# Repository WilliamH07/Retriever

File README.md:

<div align="center">

# Retriever

**Open source autonomous outdoor mobile robot**

[Architecture](docs/architecture/) ·
[Getting started](docs/DEMARRAGE.md) ·
[Bench reports](docs/bancs/) ·
[Hardware](hardware/) ·
[Support the project](#supporting-the-project)

</div>

---

## What this is

Retriever is a four wheel drive outdoor robot, built by one person and released
as open hardware. Its single objective is autonomous outdoor navigation with
ROS 2 Jazzy and Nav2, on a chassis anyone can reproduce from documented,
commodity parts.

It is an open rebuild inspired by the [Clearpath
Husky](https://clearpathrobotics.com/husky-a300-unmanned-ground-vehicle-robot/),
a reference platform in mobile robotics labs. The Husky is an excellent machine,
priced as a commercial product. Retriever asks a different question: how much of
that capability can one person reach from recovered and off the shelf parts, if
the engineering is done properly rather than cheaply?

The hardware is deliberately ordinary. The discipline applied to it is not: an
architecture dossier written before the first part was cut, a failure mode
analysis, a hardware safety chain no software can override, and a measurable
exit criterion at every stage.

## Status

<div align="center">

</div>

| Stage | Exit criterion | State |
|:-----:|----------------|-------|
| 1 | Architecture dossier and CAD complete | done |
| 2 | Chassis fabricated and assembled | done |
| 2b | First sensors published to ROS 2 over a transport agnostic link | done: [IMU](docs/bancs/imu.md) at 99.8 Hz, [lidar](docs/bancs/lidar.md) |
| 2c | Motor bench: hub motors driven from Foxglove | **current**: [coded, first spin due](docs/bancs/moteurs.md) |
| 3 | Three PCBs redesigned, power chain energised, no motor connected | next |
| 4 | Motors driven, wheels raised, all stop tests pass | planned |
| 5 | Autonomous outdoor navigation to a waypoint | planned |

Beyond stage 5, the plan is to mount a [Niryo
One](https://github.com/NiryoRobotics/niryo_one) arm and turn Retriever into a
mobile manipulator.

<div align="center">

</div>

## System architecture

<div align="center">

</div>

Three decisions shape everything else.

**A CAN bus, not USB, carries every command.** Four BLDC drivers chopping tens
of amps within 30 cm of the signal wiring make USB the wrong choice for the
control path: it is master slave, dynamically enumerated, with no frame
priority. CAN 2.0A at 500 kbit/s links the computer to every microcontroller.
USB is kept for high bandwidth perception, whose loss degrades the mission but
cannot cause dangerous motion. On the bench today the same frames travel over
serial; one Kconfig option and one launch parameter switch to CAN.

**The main computer never does real time.** It runs perception, localisation,
Nav2 and the mission, and produces setpoints. A dedicated safety
microcontroller decides whether they may be executed: the computer requests
arming, the safety node grants or refuses it.

**Safety is hardware, and independent of software.** Six stop levels, from a
100 ms software collision monitor down to a latching emergency stop and a
manual battery isolator. The last two contain no code at all.

<div align="center">

</div>

## Power

<div align="center">

</div>

The contactor is designed onto the power board rather than bought: a
`TPS4810-Q1` driving two opposed MOSFETs cuts a fault in 4.3 µs, draws 4 mW
instead of a coil's 2 to 8 W, and can test itself. The trade off is documented
in [`12-contacteur-statique.md`](docs/architecture/12-contacteur-statique.md).

## Hardware at a glance

| | |
|---|---|
| Configuration | 4WD skid steer, outdoor |
| Structure | Aluminium extrusion frame, laser cut panels, 3D printed mounts |
| Target mass | 35 kg in running order |
| Target speed | 1.5 m/s, slopes up to 10 % |
| Drivetrain | 4 × 6.5 inch hoverboard hub motors, 250 W each, 15 pole pairs |
| Motor drivers | 4 × ZS-X11H BLDC drivers, two per motor node |
| Battery | Xiaomi M365 Pro pack, 10S4P, 37 V nominal (30 to 42 V), 474 Wh |
| Endurance | about 2 h at 200 W average (estimate, 85 % depth of discharge) |
| Compute | Youyeetoo X1 (Celeron N5105), Ubuntu 24.04, ROS 2 Jazzy |
| Real time | 3 × ESP32 (SAFETY, MOTION front, MOTION rear) on CAN 2.0A, 500 kbit/s |
| Sensors | BNO085 IMU (SPI), YDLIDAR X4, GNSS; outdoor lidar and depth camera wanted |
| Localisation | GNSS, IMU and wheel odometry, dual EKF |
| Navigation | Nav2, collision monitor, twist mux |

## Repository layout

```
docs/
  architecture/   the design dossier: 00–07 base, 08–12 PCB and errata, 13 software
  bancs/          bench reports: IMU, lidar, motors (French)
  DEMARRAGE.md    getting started, from a blank machine to /imu/data (French)
  measurements/   bench measurements that gate the hardware design
  foxglove/       Foxglove Studio layouts for each bench
  images/         renders, build photos, diagrams
  sponsorship/    the sponsorship dossier
  archive/        superseded work, kept for history
hardware/
  icd.yaml        interface control document: every connector, every pin
  pcb/            the three boards, being redesigned
  cad/            laser cut DXF profiles, mechanical notes
  bom/            pointer to the costed bill of materials
firmware/
  protocol/       protocol.yaml, the single source of truth, and its generator
  components/     link layer, protocol header, BNO085 driver
  esp32_safety/   safety node (IMU bench today)
  esp32_motion/   motor node, front and rear
  test/           host tests, no hardware needed
ros2_ws/src/
  retriever_link/       transport agnostic bridge: serial today, SocketCAN later
  retriever_protocol/   generated protocol header for ROS 2
  retriever_msgs/       message definitions
  retriever_bringup/    launch files and bench configurations
  retriever_*           description, hardware, control, navigation, teleop: planned
tools/            bench scripts, flashing, protocol and link checks
```

## Documentation

The design documentation is in French; an English summary is planned. Every
claim carries a marker: verified against a datasheet, community consensus, to
be measured, or an explicit assumption.

| Start with | Why |
|---|---|
| [Documentation index](docs/README.md) | One page that says what each document is for and whether it is current |
| [Démarrage](docs/DEMARRAGE.md) | Install, flash an ESP32, build the workspace, verify the IMU chain stage by stage |
| [Bench reports](docs/bancs/) | What runs today, with measured numbers, and the silent defects found on the way |
| [Architecture dossier](docs/architecture/) | Power, communications, ROS 2, safety, network, BOM and FMEA, operator console |
| [Corrections v1.2](docs/architecture/11-corrections-v1.2.md) | Takes precedence over 00–07 wherever they disagree |

## Supporting the project

Retriever is self funded by a student. Four items stand between the current
platform and autonomous outdoor operation:

- **Printed circuit boards.** Three boards are being redesigned from a clean
  sheet: a motor interface, a safety and power board, and a passive CAN and
  safety bus distribution board.
- **Embedded AI compute.** The current x86 board runs the navigation stack, but
  not the perception outdoor autonomy asks for.
- **An outdoor lidar.** The blocking item. The 2D lidar on hand is specified for
  indoor use, and direct sunlight saturates its receiver.
- **A depth camera.** The Kinect v2 on hand is blind in daylight and its driver
  has been unmaintained since 2021.

Sponsors get a written and filmed integration tutorial for the sponsored part,
a field test video with honest performance data, attribution on the chassis and
here, and private feedback on how the part behaves on a real robot before
anything is published.

The full dossier is in [docs/sponsorship](docs/sponsorship/). Enquiries welcome:
see contact below.

## Credits

Inspired by the Clearpath Husky platform. The mechanical design was modelled
from scratch and the electrical and software architecture designed
independently. Some ROS 2 package conventions follow the open source
[husky/husky](https://github.com/husky/husky) repository, published under BSD 3
Clause. Clearpath Robotics is not affiliated with this project and does not
endorse it.

See [CREDITS.md](CREDITS.md) for the full attribution, and
[CONTRIBUTING.md](CONTRIBUTING.md) before opening a pull request.

## Licence

Software and firmware are released under the [Apache License 2.0](LICENSE).
Hardware designs, CAD and PCB files are released under the [CERN Open Hardware
Licence Version 2, Strongly Reciprocal](LICENSE-HARDWARE.txt).

## Contact

William Hanczyk, Bordeaux, France
wcontact33@gmail.com

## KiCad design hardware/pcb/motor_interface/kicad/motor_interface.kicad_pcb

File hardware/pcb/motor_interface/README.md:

# motor_interface

> **v2.0-draft — do not fabricate before M7, HALL_OC, P1, P2, P3.** Schematic and
> layout generated, ERC and DRC clean (ERC 0, DRC 0 with schematic parity and all severities, 0 unconnected). Every choice and its reason:
> [`decisions.md`](decisions.md) (French). Brief:
> [`cahier-des-charges.md`](cahier-des-charges.md).

| | |
|---|---|
| Size | 100 × 100 mm, 4 layers, 4 × M3, antenna notch on the right edge |
| Parts | 123 placed by the assembler (117 SMD + 6 Micro-Fit 6-way); hand-soldered: 2 × Micro-Fit 8-way, 2 × Mill-Max sockets; 14 option footprints not fitted; 20 named test pads |
| Module | ESP32-DevKitC V4 on two 1 × 19 turned-pin sockets, rows 25.40 mm apart (P1 to confirm) |
| Sources | [`kicad/`](kicad/) — KiCad 10 project, **generated** by [`scripts/build.py`](scripts/build.py) |
| Fabrication | [`fab/`](fab/) — Gerber zip, JLCPCB BOM and placement, schematic PDF, renders |

Rebuild everything: `./build.sh` (routing takes several minutes) then `./fab.sh`
(needs the toolchain in [`../outils.md`](../outils.md)). Do not edit the KiCad files
by hand: change `scripts/build.py` and rebuild.

Sits between a MOTION ESP32 and two ZS-X11H drivers with their hub motors. One
reference, two boards in service (front and rear), three spares from a lot of five.
The role is set by a solder jumper read through the ADS1115, not by GPIO straps.

The specification of record is
[`10-spec-motor-interface.md`](../../../docs/architecture/10-spec-motor-interface.md).
The earlier four-motor board is archived in
[`docs/archive/pcb-v1/`](../../../docs/archive/pcb-v1/).

## What changed against the specification (13 November 2026)

| Point | Spec / ICD v1.2 | This board | Why |
|---|---|---|---|
| `5V_BRAKE` | through J5/J6 pin 7, 2200 µF on board | **not on this board**, pin 7 NC | Decision D5: unplugging the board must keep the brake applied |
| Power input | J7 and trunk pin 1 | **trunk only**, J7 removed | One source, nothing to arbitrate |
| Grounds | undefined | **`GND`, `GND_MOT_A`, `GND_MOT_B` kept apart**, bench-only 0 Ω ties not fitted | Decision D4: single star point on `safety_power` |
| DAC supply | 5 V | **3.3 V**, internal 2.048 V reference, op-amp gain 2.5 | `MCP4728` VIH = 0.7 VDD, unreachable from a 3.3 V bus at 5 V |
| Low-side switches | `DMG1012T` (SOT-523) | **`AO3400A`** (SOT-23, JLCPCB basic) | 48 mΩ guaranteed at VGS 2.5 V, hand-reworkable |
| Polarity options | on `DIR`, `STOP`, `EL` | **`DIR` and `STOP` only** | Any option on `EL` could defeat the fail-safe |
| Hall PPTC | 30 mA on the pull-up tap | **removed** | Separate `+5V_MOT_A/B` nets; no PPTC of that size trips before the 78L05 |
| Hall activity LEDs | six | **none** | Test points and the serial console do the same job |

## Scope

| Function | Implementation |
|---|---|
| Hall passthrough | J1→J3, J2→J4: five straight 0.8 mm tracks each, one layer, no via, no part in series |
| Hall tap | 2.2 kΩ pull-up (population option, HALL_OC), 2.2 kΩ + 10 nF / 100 V, `BAT54S` clamp, referenced to `GND_MOT_x`; `SN74LVC3G17` at 3.3 V (Ioff) |
| Speed command | `MCP4728` (3.3 V, internal ref.) → `TLV9062` ×2.5 → `VR`, 0 V with the module out |
| `DIR`, `STOP` | `AO3400A` open drain, gate pull-down; pull-up / pull-down / direct-drive footprints not fitted |
| Brake `EL` | per wheel `74LVC1G08` (`GPIO26` AND `/SAFE`) → `AO3400A`; pull-up on the harness |
| Temperatures, role, revision | `ADS1115` at 0x48: NTC A, NTC B, role divider (SJ1/SJ2), revision divider (½ = v2.0) |
| Watchdog | `TPL5010`, 2 s, `RSTn` on the module `EN` (D7) |
| CAN | `TCAN1042HVDR`, `STB` grounded, `VIO` 3.3 V, `NUP2105L`, `ACT45B`, no termination |
| Power | trunk 5 V → `AO3401A` reverse protection → `SMAJ6.0A` → `LM66100` → module 5 V; 3.3 V from the module |

## Blocking measurements

M7 (Hall output level and impedance), HALL_OC (open collector or push-pull),
HALL_COL (wire colours, silkscreen), P1 to P3 on the ESP32 module (row spacing, pin
order, PSRAM variant). See [`docs/measurements/`](../../../docs/measurements/).

Pinout: `boards.motor_interface` in [`hardware/icd.yaml`](../../icd.yaml) (v1.2; the
changes this board needs for v1.3 are listed at the end of [`decisions.md`](decisions.md)).

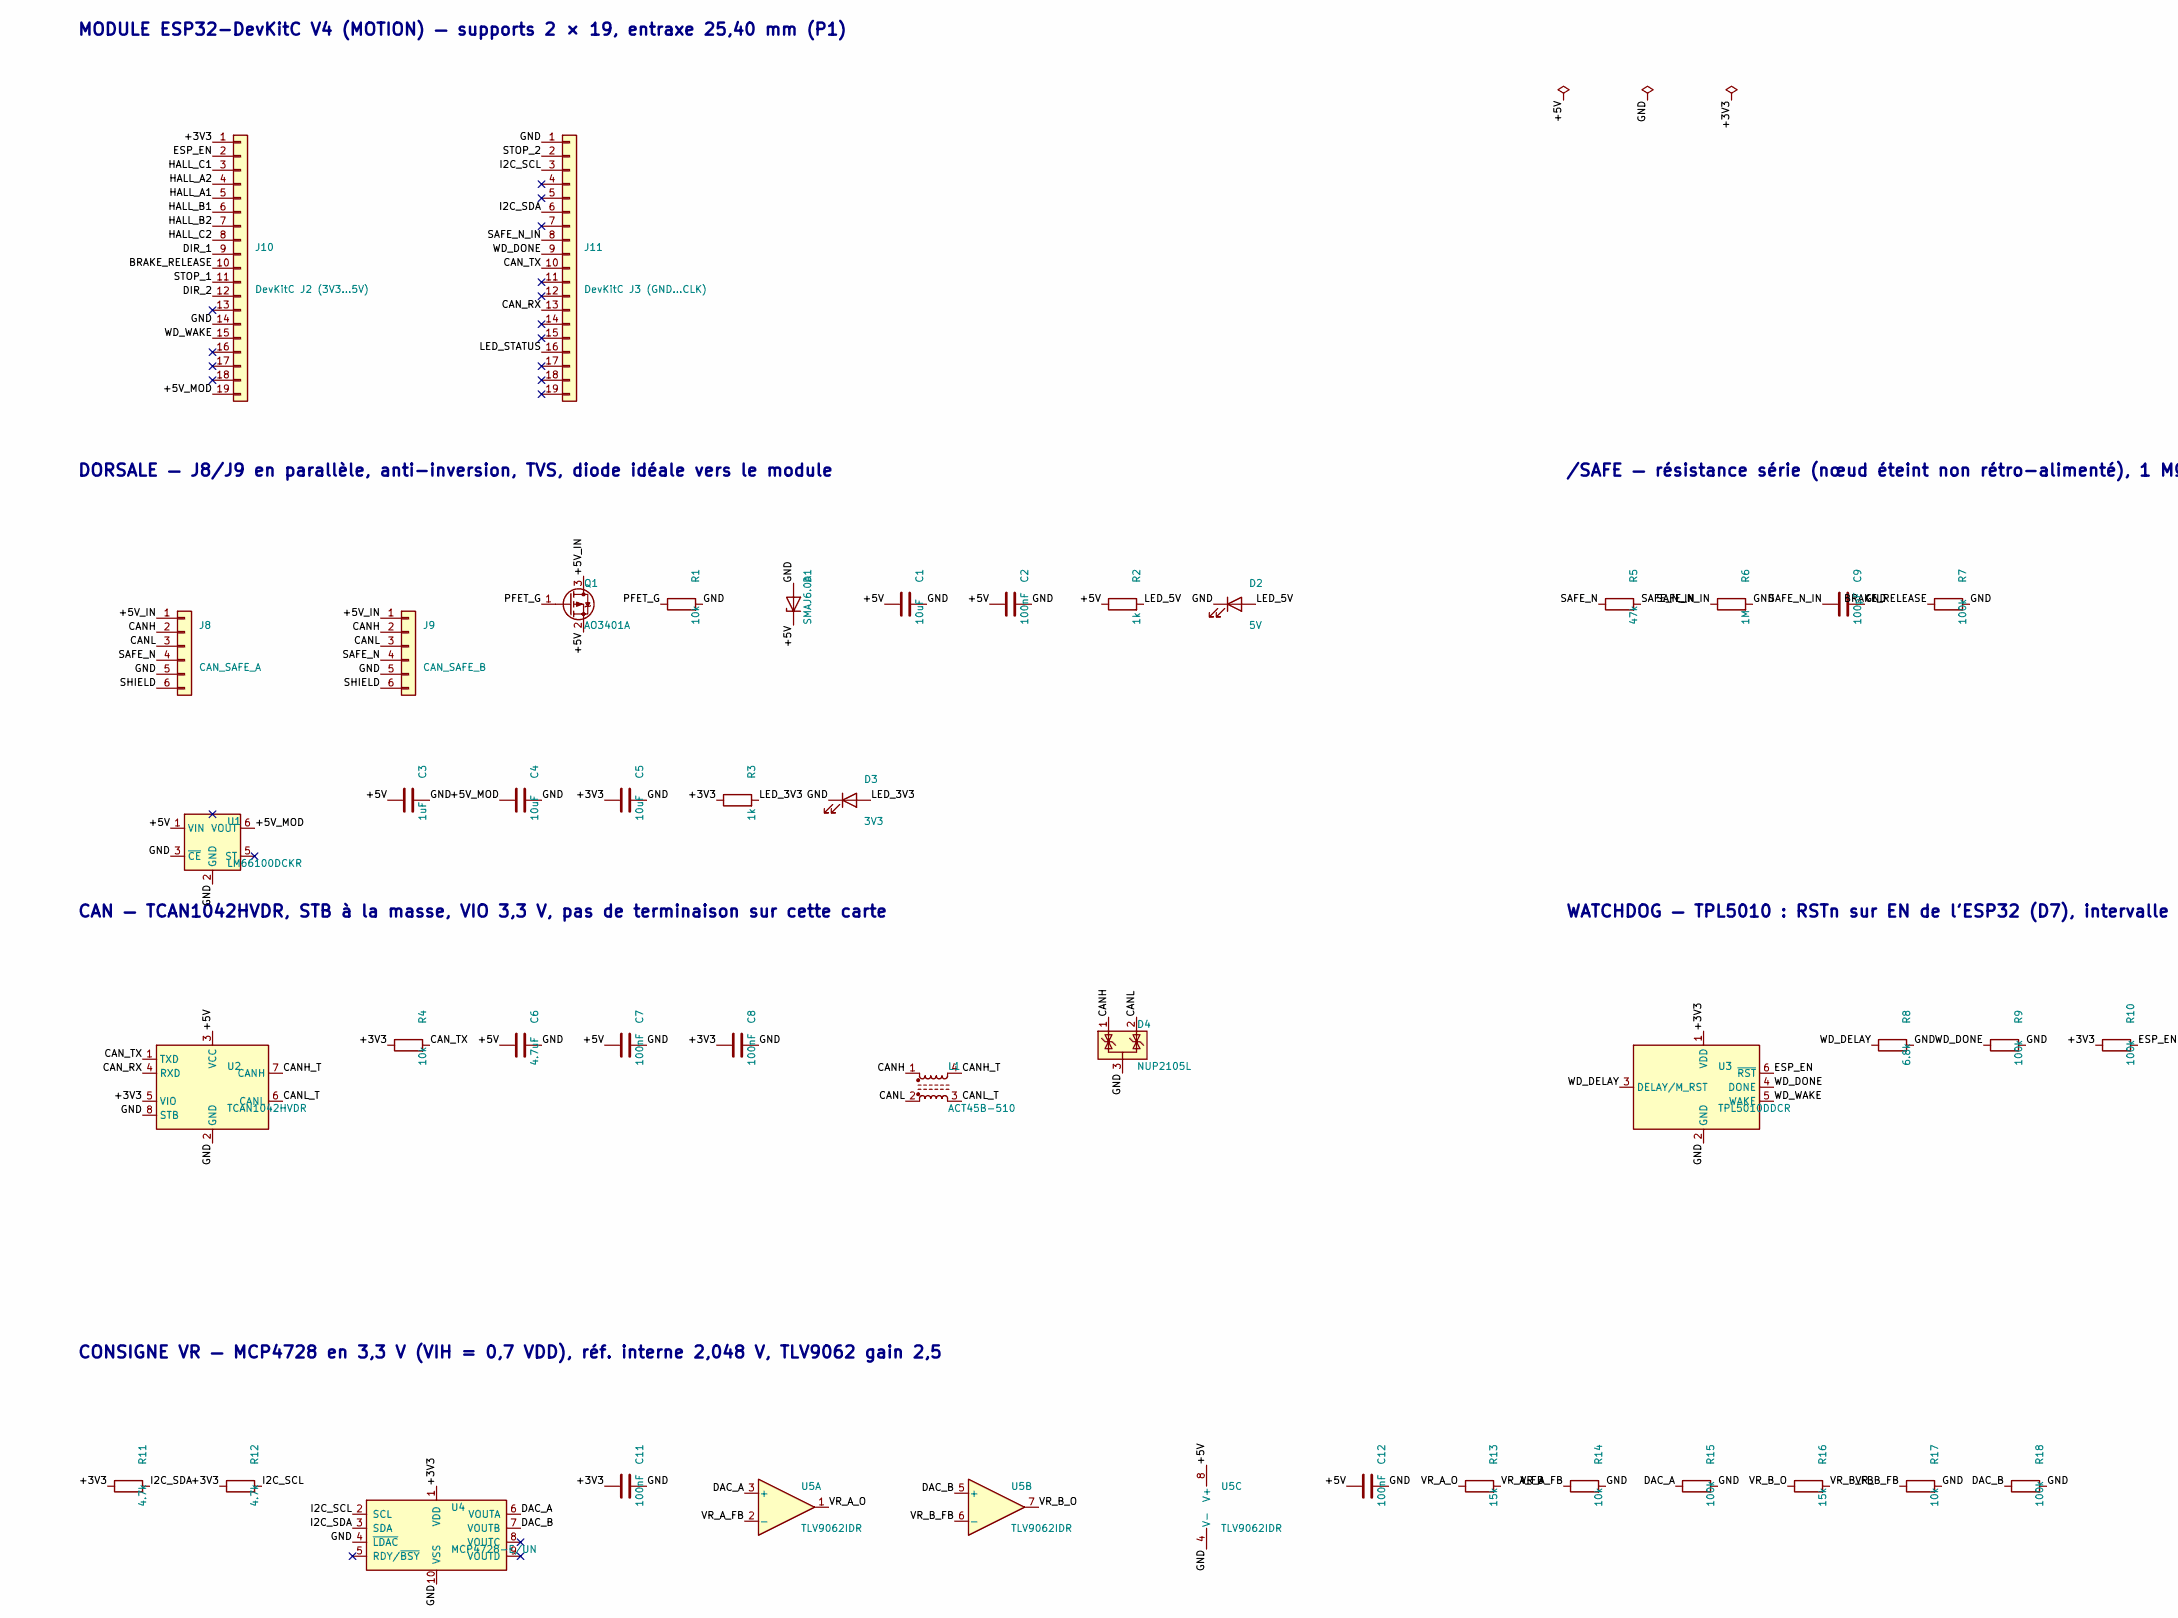
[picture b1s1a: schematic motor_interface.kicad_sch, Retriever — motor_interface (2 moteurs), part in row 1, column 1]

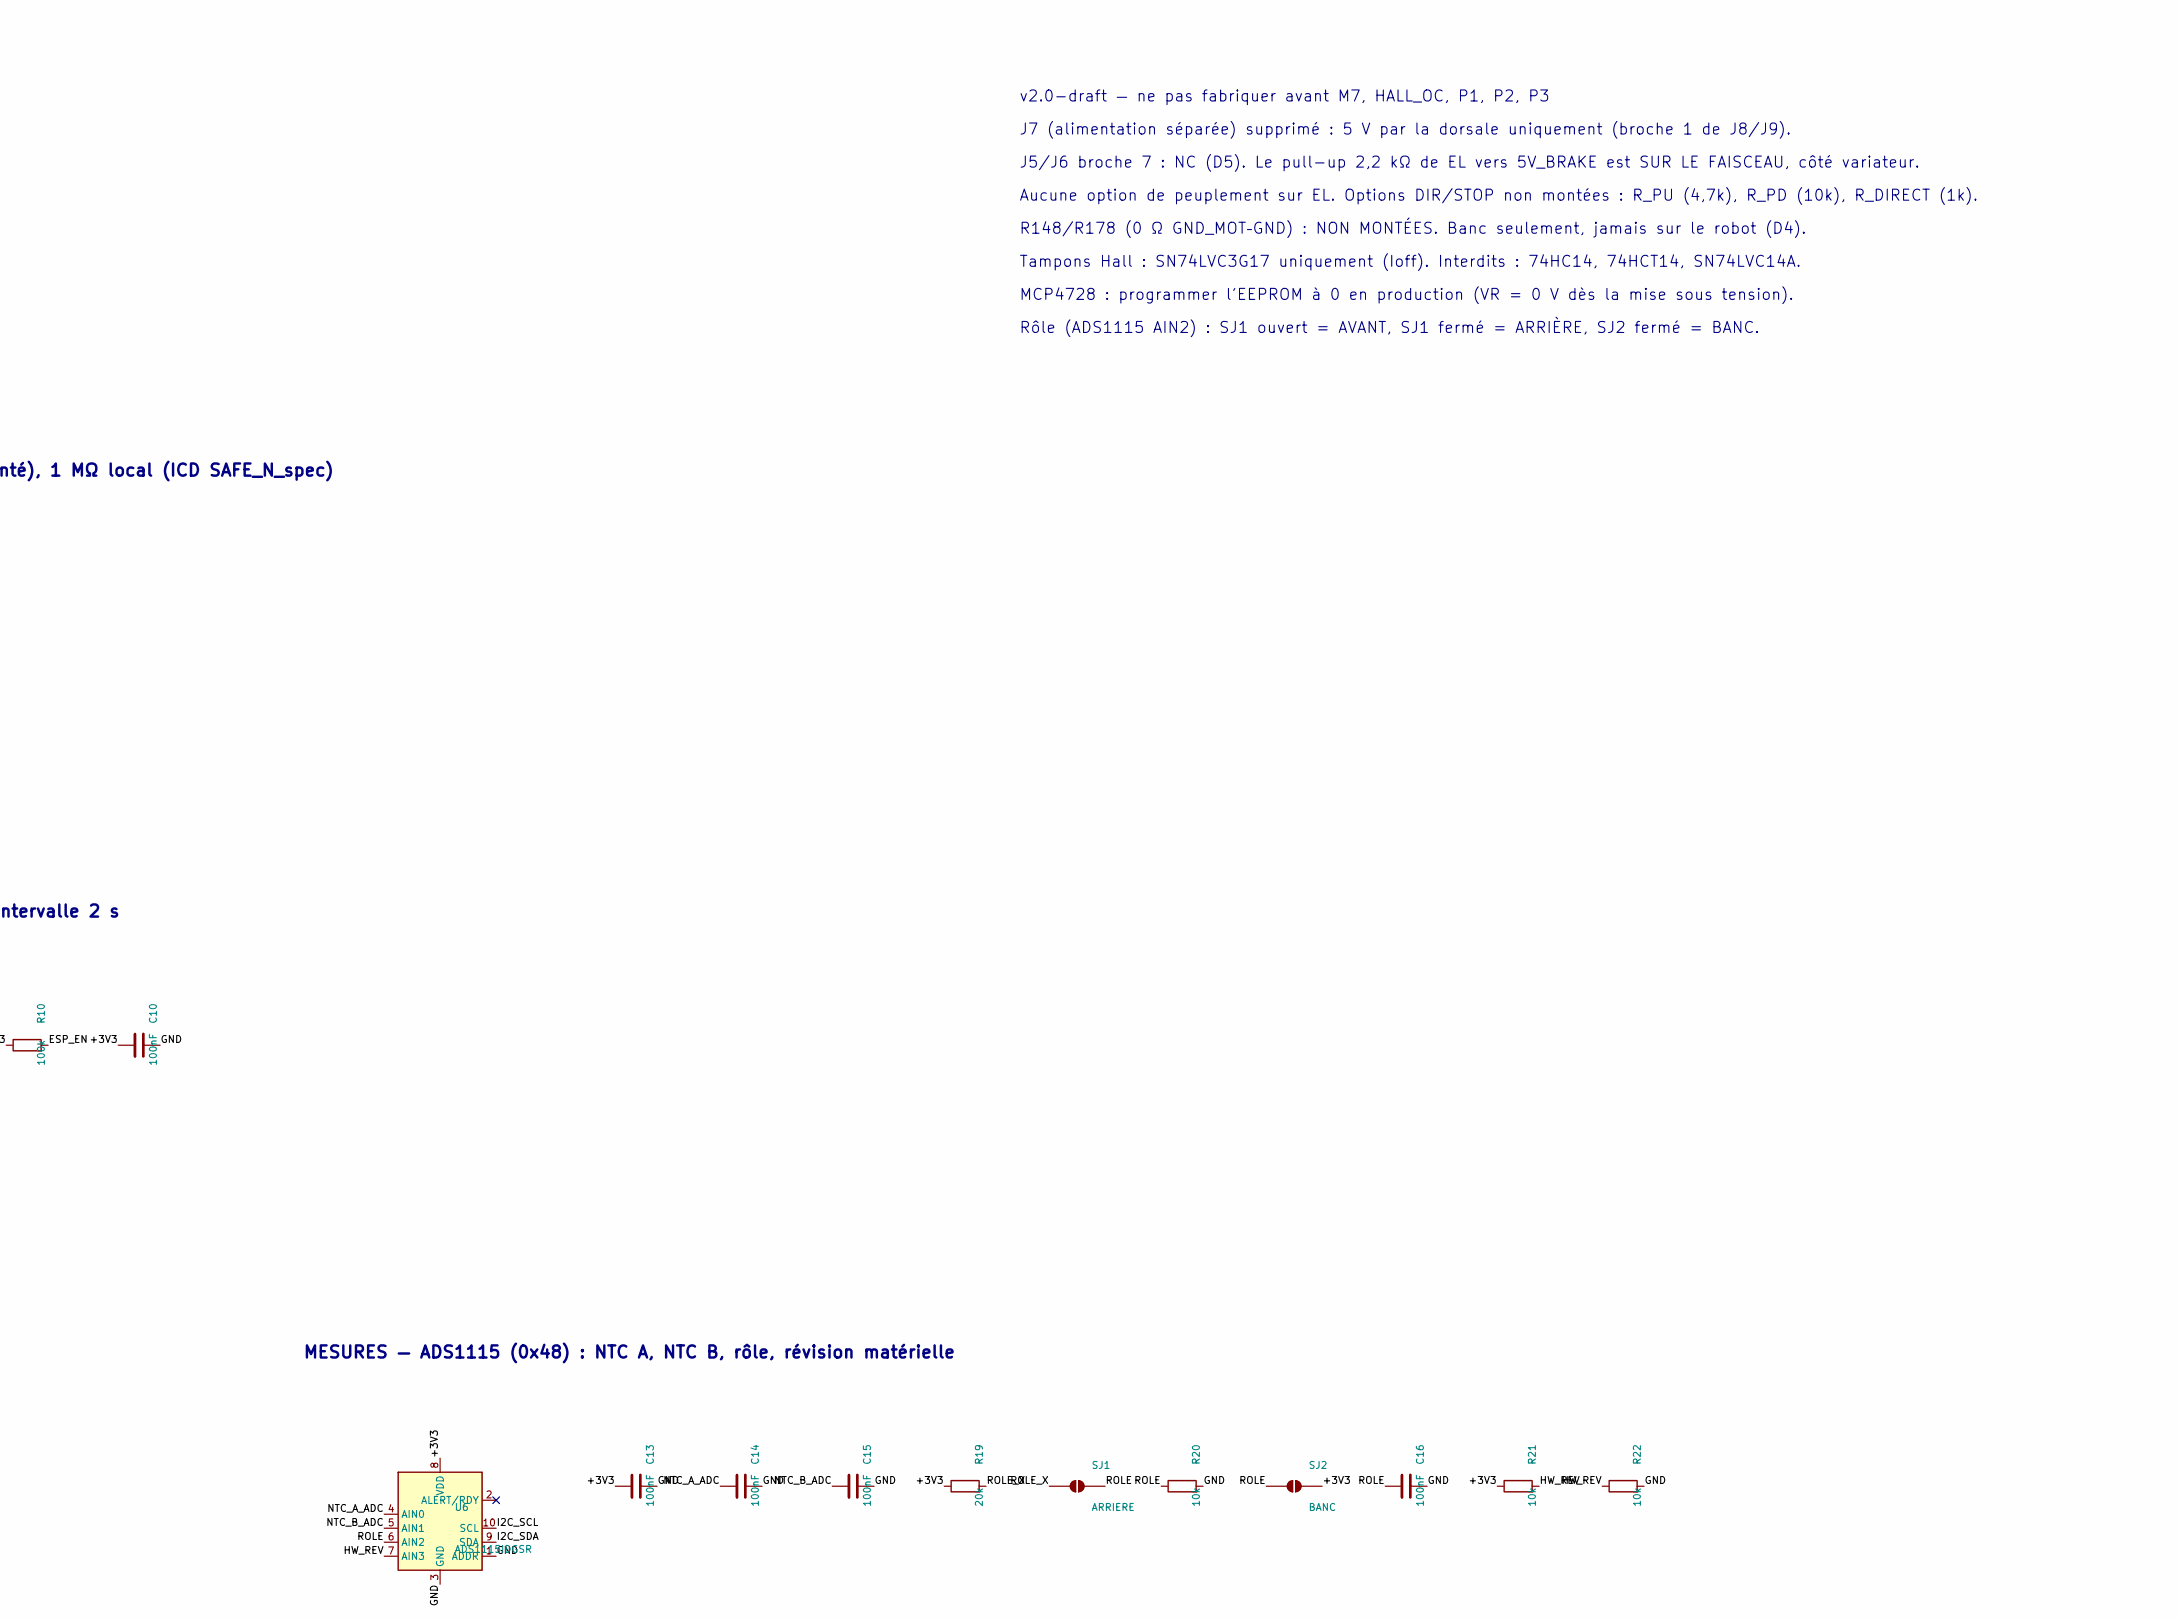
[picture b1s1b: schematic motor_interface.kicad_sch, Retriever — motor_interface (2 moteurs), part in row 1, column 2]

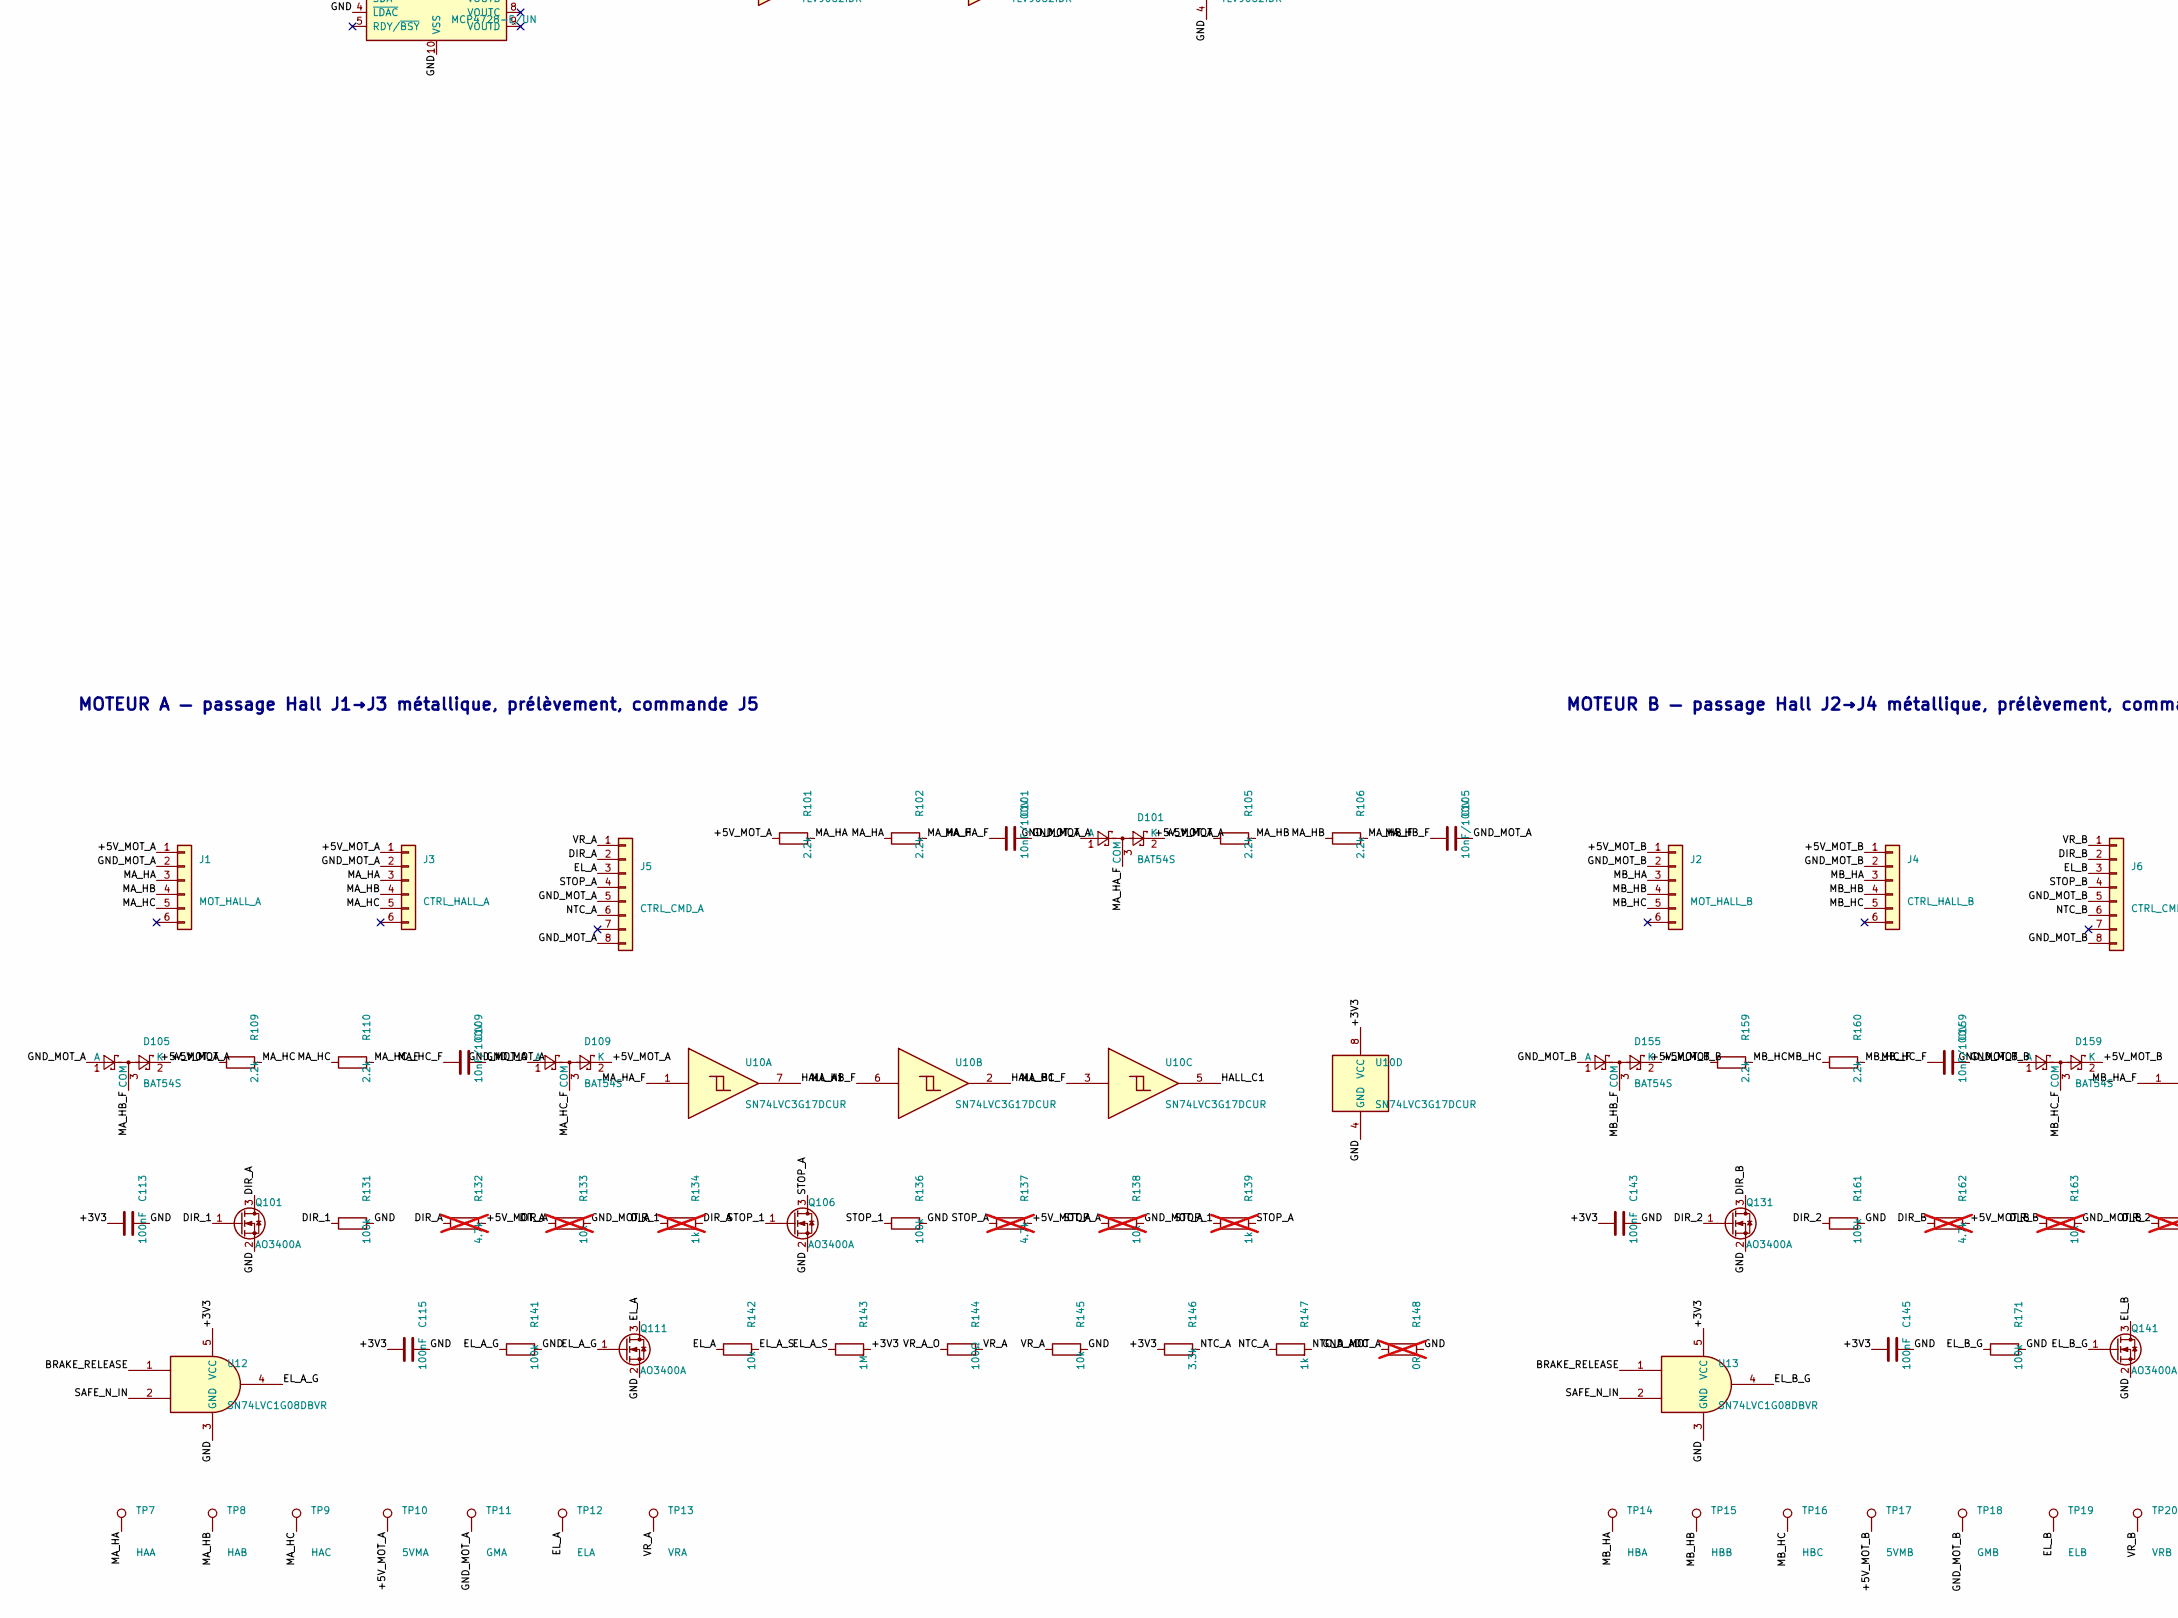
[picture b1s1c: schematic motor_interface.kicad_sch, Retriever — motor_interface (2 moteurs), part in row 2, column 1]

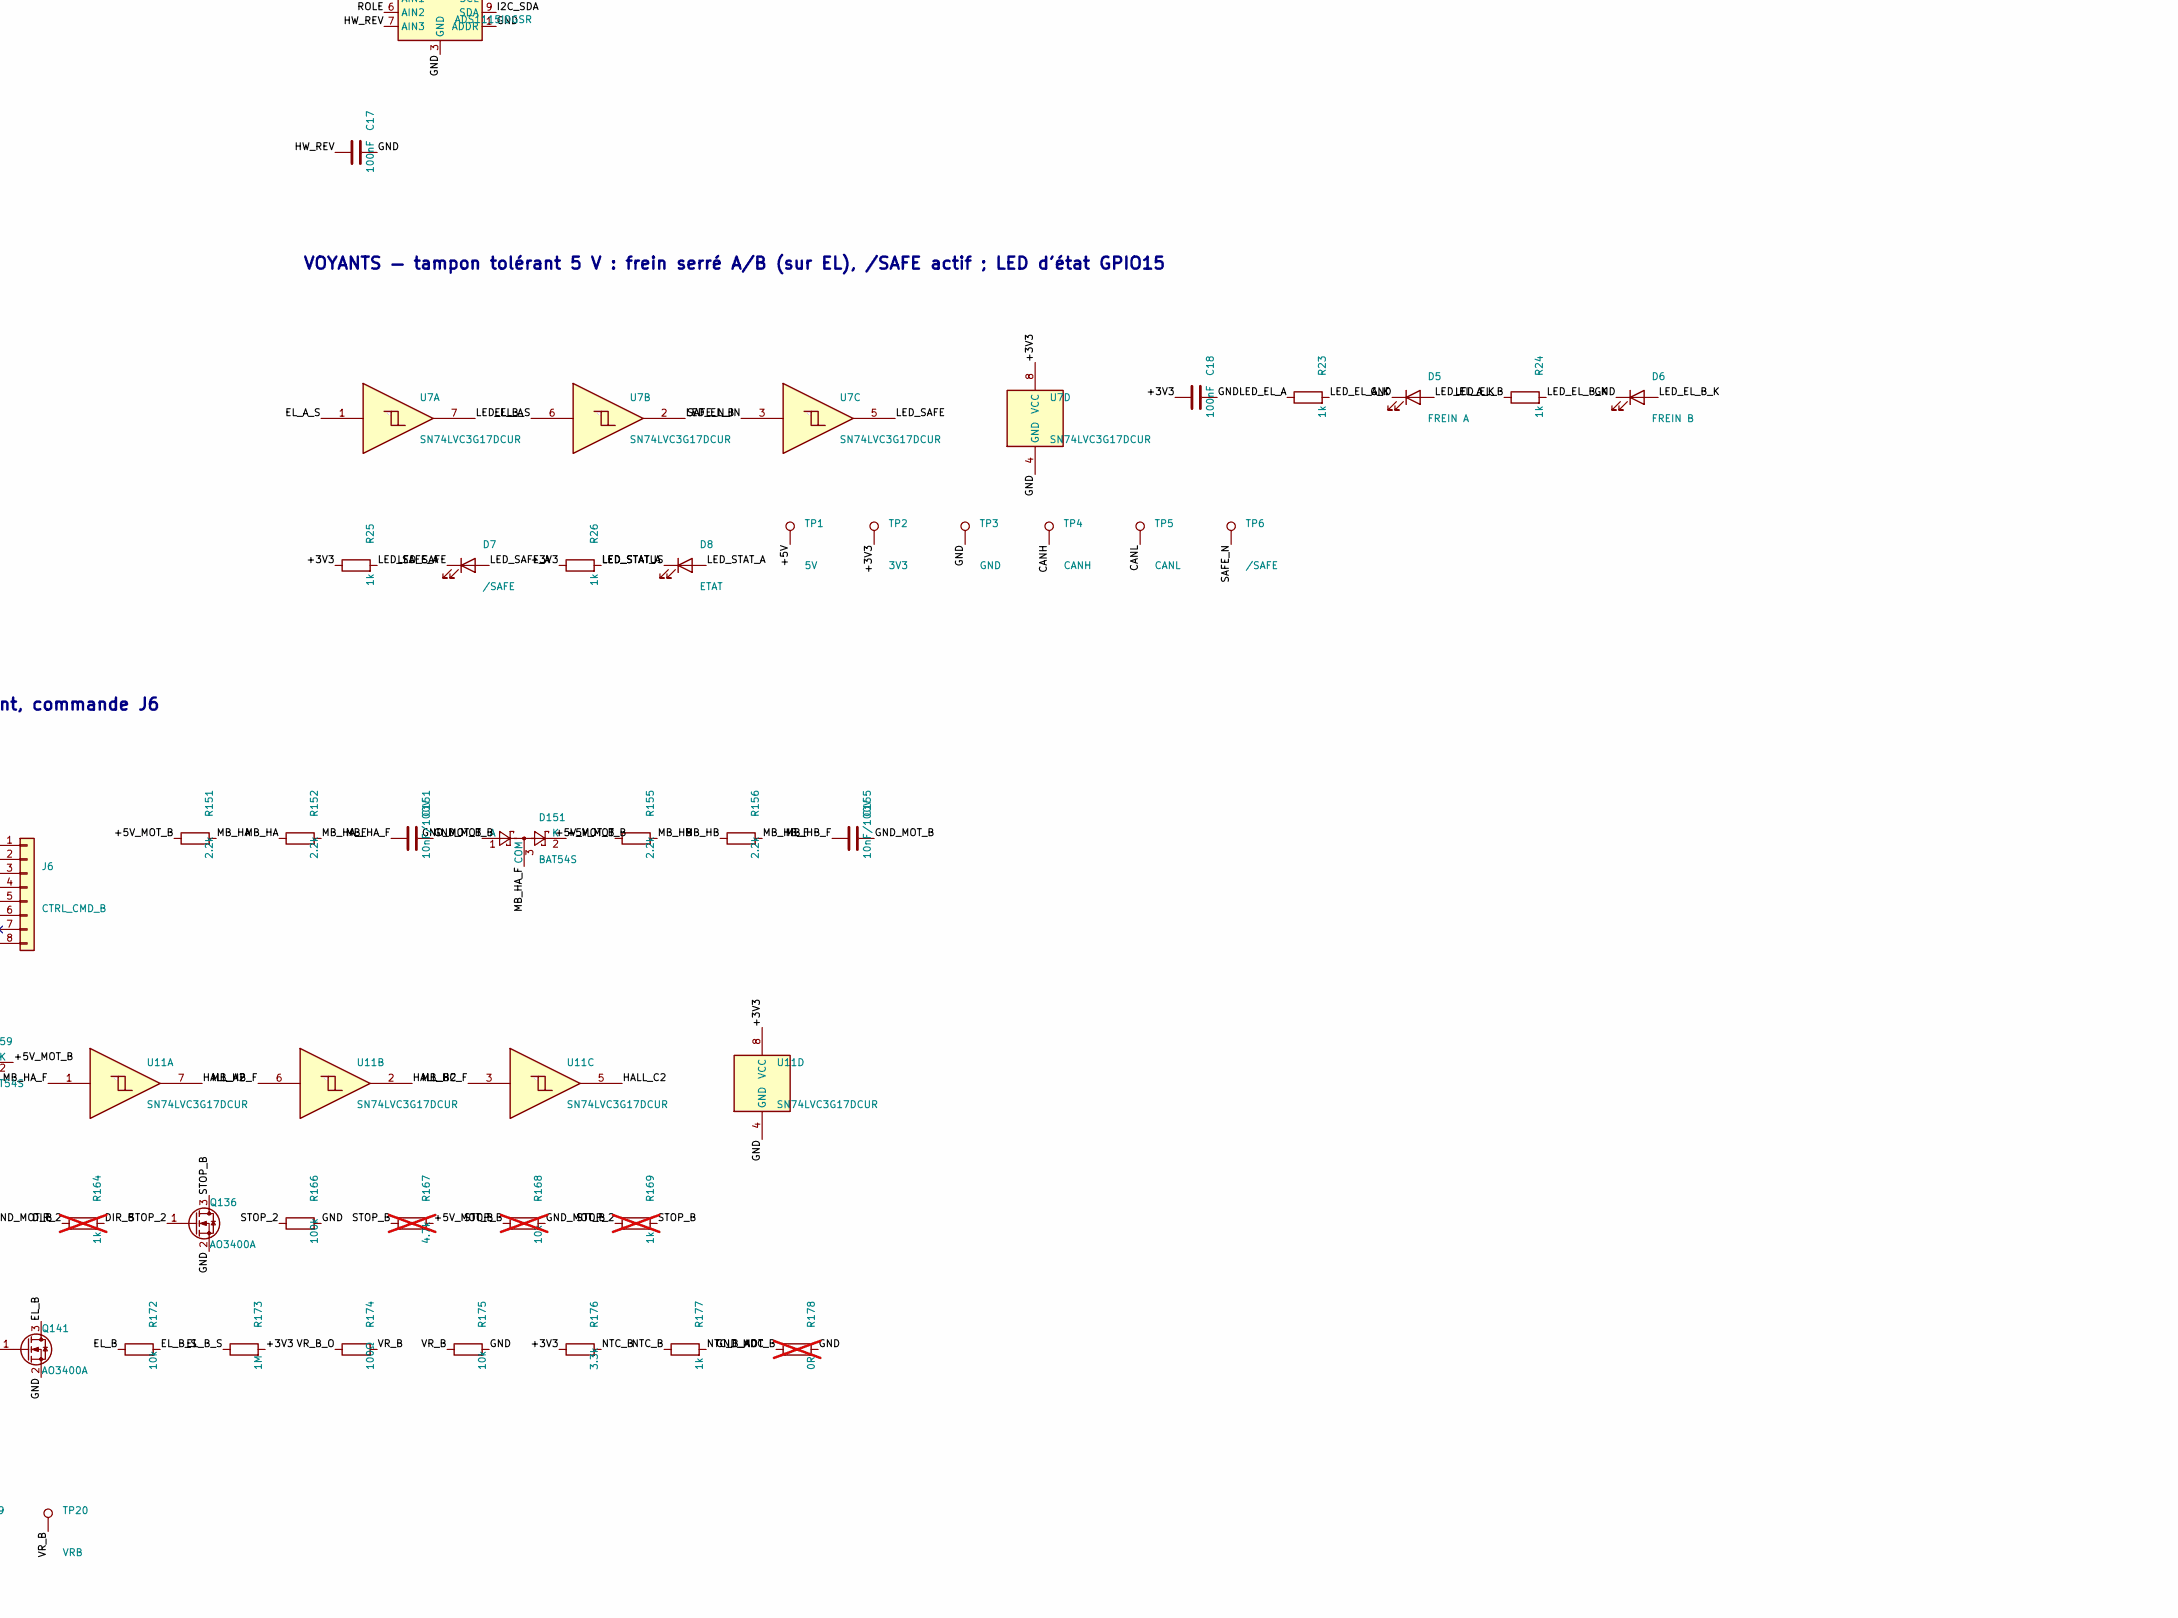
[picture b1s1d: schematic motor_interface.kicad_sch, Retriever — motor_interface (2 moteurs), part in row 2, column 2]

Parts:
C1, C4, C5: 10uF; C_0805_2012Metric; MPN CL21A106KAYNNNE; LCSC C15850
C2, C7, C8, C10, C11, C12, C13, C14, C15, C16, C17, C18, C113, C115, C143, C145: 100nF; C_0603_1608Metric; MPN CC0603KRX7R9BB104; LCSC C14663
C3: 1uF; C_0603_1608Metric; MPN CL10A105KB8NNNC; LCSC C15849
C6: 4.7uF; C_0805_2012Metric; MPN CL21A475KAQNNNE; LCSC C1779
C9: 100pF; C_0603_1608Metric; MPN CC0603JRNPO9BN101; LCSC C14858
C101, C105, C109, C151, C155, C159: 10nF/100V; C_0603_1608Metric; MPN FH 0603B103K101NT; LCSC C43253
D1: SMAJ6.0A; D_SMA; MPN Littelfuse SMAJ6.0A; LCSC C223993
D2: 5V; LED_0603_1608Metric; MPN Everlight 19-217/GHC; LCSC C72043
D3: 3V3; LED_0603_1608Metric; MPN Everlight 19-217/GHC; LCSC C72043
D4: NUP2105L; SOT-23; MPN onsemi NUP2105LT1G; LCSC C14486
D5: FREIN A; LED_0603_1608Metric; MPN Hubei KENTO KT-0603R; LCSC C2286
D6: FREIN B; LED_0603_1608Metric; MPN Hubei KENTO KT-0603R; LCSC C2286
D7: /SAFE; LED_0603_1608Metric; MPN Hubei KENTO KT-0603R; LCSC C2286
D8: ETAT; LED_0603_1608Metric; MPN Everlight 19-217/BHC; LCSC C72041
D101, D105, D109, D151, D155, D159: BAT54S; SOT-23; MPN Nexperia BAT54S,215; LCSC C47546
J1: MOT_HALL_A; Molex_Micro-Fit_3.0_43650-0615_1x06_P3.00mm_Vertical; MPN Molex 43650-0615; LCSC C505231
J2: MOT_HALL_B; Molex_Micro-Fit_3.0_43650-0615_1x06_P3.00mm_Vertical; MPN Molex 43650-0615; LCSC C505231
J3: CTRL_HALL_A; Molex_Micro-Fit_3.0_43650-0615_1x06_P3.00mm_Vertical; MPN Molex 43650-0615; LCSC C505231
J4: CTRL_HALL_B; Molex_Micro-Fit_3.0_43650-0615_1x06_P3.00mm_Vertical; MPN Molex 43650-0615; LCSC C505231
J5: CTRL_CMD_A; Molex_Micro-Fit_3.0_43650-0815_1x08_P3.00mm_Vertical; MPN Molex 43650-0815 (Mouser 538-43650-0815)
J6: CTRL_CMD_B; Molex_Micro-Fit_3.0_43650-0815_1x08_P3.00mm_Vertical; MPN Molex 43650-0815 (Mouser 538-43650-0815)
J8: CAN_SAFE_A; Molex_Micro-Fit_3.0_43650-0615_1x06_P3.00mm_Vertical; MPN Molex 43650-0615; LCSC C505231
J9: CAN_SAFE_B; Molex_Micro-Fit_3.0_43650-0615_1x06_P3.00mm_Vertical; MPN Molex 43650-0615; LCSC C505231
J10: DevKitC J2 (3V3…5V); PinSocket_1x19_P2.54mm_Vertical; MPN Mill-Max 310-43-119-41-001000 (Mouser)
J11: DevKitC J3 (GND…CLK); PinSocket_1x19_P2.54mm_Vertical; MPN Mill-Max 310-43-119-41-001000 (Mouser)
L1: ACT45B-510; IND-SMD_4P-L4.5-W3.2-TL; MPN TDK ACT45B-510-2P-TL003; LCSC C76584
Q1: AO3401A; SOT-23; MPN AOS AO3401A; LCSC C15127
Q101, Q106, Q111, Q131, Q136, Q141: AO3400A; SOT-23; MPN AOS AO3400A; LCSC C20917
R1, R4, R14, R17, R20, R21, R22, R142, R145, R172, R175: 10k; R_0603_1608Metric; MPN 0603WAF1002T5E; LCSC C25804
R2, R3, R23, R24, R25, R26, R147, R177: 1k; R_0603_1608Metric; MPN 0603WAF1001T5E; LCSC C21190
R5: 47k; R_0603_1608Metric; MPN 0603WAF4702T5E; LCSC C25819
R6, R143, R173: 1M; R_0603_1608Metric; MPN 0603WAF1004T5E; LCSC C22935
R7, R9, R10, R15, R18, R131, R136, R141, R161, R166, R171: 100k; R_0603_1608Metric; MPN 0603WAF1003T5E; LCSC C25803
R8: 6.8k; R_0603_1608Metric; MPN 0603WAF6801T5E; LCSC C23212
R11, R12: 4.7k; R_0603_1608Metric; MPN 0603WAF4701T5E; LCSC C23162
R13, R16: 15k; R_0603_1608Metric; MPN 0603WAF1502T5E; LCSC C22809
R19: 20k; R_0603_1608Metric; MPN 0603WAF2002T5E; LCSC C4184
R101, R102, R105, R106, R109, R110, R151, R152, R155, R156, R159, R160: 2.2k; R_0603_1608Metric; MPN 0603WAF2201T5E; LCSC C4190
R132, R137, R162, R167: 4.7k; R_0603_1608Metric; MPN 0603WAF4701T5E; LCSC C23162; not fitted
R133, R138, R163, R168: 10k; R_0603_1608Metric; MPN 0603WAF1002T5E; LCSC C25804; not fitted
R134, R139, R164, R169: 1k; R_0603_1608Metric; MPN 0603WAF1001T5E; LCSC C21190; not fitted
R144, R174: 100Ω; R_0603_1608Metric; MPN 0603WAF1000T5E; LCSC C22775
R146, R176: 3.3k; R_0603_1608Metric; MPN 0603WAF3301T5E; LCSC C22978
R148, R178: 0R; R_0603_1608Metric; MPN 0603WAF0000T5E; LCSC C21189; not fitted
SJ1: ARRIERE; SolderJumper-2_P1.3mm_Open_RoundedPad1.0x1.5mm
SJ2: BANC; SolderJumper-2_P1.3mm_Open_RoundedPad1.0x1.5mm
TP1: 5V; TestPoint_Pad_D1.5mm
TP2: 3V3; TestPoint_Pad_D1.5mm
TP3: GND; TestPoint_Pad_D1.5mm
TP4: CANH; TestPoint_Pad_D1.5mm
TP5: CANL; TestPoint_Pad_D1.5mm
TP6: /SAFE; TestPoint_Pad_D1.5mm
TP7: HAA; TestPoint_Pad_D1.5mm
TP8: HAB; TestPoint_Pad_D1.5mm
TP9: HAC; TestPoint_Pad_D1.5mm
TP10: 5VMA; TestPoint_Pad_D1.5mm
TP11: GMA; TestPoint_Pad_D1.5mm
TP12: ELA; TestPoint_Pad_D1.5mm
TP13: VRA; TestPoint_Pad_D1.5mm
TP14: HBA; TestPoint_Pad_D1.5mm
TP15: HBB; TestPoint_Pad_D1.5mm
TP16: HBC; TestPoint_Pad_D1.5mm
TP17: 5VMB; TestPoint_Pad_D1.5mm
TP18: GMB; TestPoint_Pad_D1.5mm
TP19: ELB; TestPoint_Pad_D1.5mm
TP20: VRB; TestPoint_Pad_D1.5mm
U1: LM66100DCKR; SOT-363_SC-70-6; MPN TI LM66100DCKR; LCSC C2869734
U2: TCAN1042HVDR; SOIC-8_3.9x4.9mm_P1.27mm; MPN TI TCAN1042HVDR; LCSC C127869
U3: TPL5010DDCR; SOT-23-6; MPN TI TPL5010DDCR; LCSC C473912
U4: MCP4728-E/UN; MSOP-10_3x3mm_P0.5mm; MPN Microchip MCP4728-E/UN; LCSC C108207
U5: TLV9062IDR; SOIC-8_3.9x4.9mm_P1.27mm; MPN TI TLV9062IDR; LCSC C398355
U6: ADS1115IDGSR; TSSOP-10_3x3mm_P0.5mm; MPN TI ADS1115IDGSR; LCSC C37593
U7, U10, U11: SN74LVC3G17DCUR; VSSOP-8_2.3x2mm_P0.5mm; MPN TI SN74LVC3G17DCUR; LCSC C68245
U12, U13: SN74LVC1G08DBVR; SOT-23-5; MPN TI SN74LVC1G08DBVR; LCSC C7666

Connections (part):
/+3V3: C5.1, C8.1, C10.1, C11.1, C13.1, C18.1, C113.1, C115.1, C143.1, C145.1, J10.1, R3.1, R4.1, R10.1, R11.1, R12.1, R19.1, R21.1, R25.1, R26.1, R143.2, R146.1, R173.2, R176.1, SJ2.2 (B), TP2.1, U2.5 (VIO), U3.1 (VDD), U4.1 (VDD), U6.8 (VDD), U7.8 (VCC), U10.8 (VCC), U11.8 (VCC), U12.5 (VCC), U13.5 (VCC)
/+5V: C1.1, C2.1, C3.1, C6.1, C7.1, C12.1, D1.1 (K), Q1.2 (S), R2.1, TP1.1, U1.1 (VIN), U2.3 (VCC), U5.8 (V+)
/+5V_IN: J8.1, J9.1, Q1.3 (D)
/+5V_MOD: C4.1, J10.19, U1.6 (VOUT)
/+5V_MOT_A: D101.2 (K), D105.2 (K), D109.2 (K), J1.1, J3.1, R101.1, R105.1, R109.1, R132.2, R137.2, TP10.1
/+5V_MOT_B: D151.2 (K), D155.2 (K), D159.2 (K), J2.1, J4.1, R151.1, R155.1, R159.1, R162.2, R167.2, TP17.1
/BRAKE_RELEASE: J10.10, R7.1, U12.1, U13.1
/CANH: D4.1 (K), J8.2, J9.2, L1.1, TP4.1
/CANH_T: L1.4, U2.7 (CANH)
/CANL: D4.2 (K), J8.3, J9.3, L1.2, TP5.1
/CANL_T: L1.3, U2.6 (CANL)
/CAN_RX: J11.13, U2.4 (RXD)
/CAN_TX: J11.10, R4.2, U2.1 (TXD)
/DAC_A: R15.1, U4.6 (VOUTA), U5.3 (+)
/DAC_B: R18.1, U4.7 (VOUTB), U5.5 (+)
/DIR_1: J10.9, Q101.1 (G), R131.1, R134.1
/DIR_2: J10.12, Q131.1 (G), R161.1, R164.1
/DIR_A: J5.2, Q101.3 (D), R132.1, R133.1, R134.2
/DIR_B: J6.2, Q131.3 (D), R162.1, R163.1, R164.2
/EL_A: J5.3, Q111.3 (D), R142.1, TP12.1
/EL_A_G: Q111.1 (G), R141.1, U12.4
/EL_A_S: R142.2, R143.1, U7.1
/EL_B: J6.3, Q141.3 (D), R172.1, TP19.1
/EL_B_G: Q141.1 (G), R171.1, U13.4
/EL_B_S: R172.2, R173.1, U7.6
/ESP_EN: J10.2, R10.2, U3.6 (~RST)
/GND: C1.2, C2.2, C3.2, C4.2, C5.2, C6.2, C7.2, C8.2, C9.2, C10.2, C11.2, C12.2, C13.2, C14.2, C15.2, C16.2, C17.2, C18.2, C113.2, C115.2, C143.2, C145.2, D1.2 (A), D2.1 (K), D3.1 (K), D4.3 (A), D5.1 (K), D6.1 (K), J8.5, J9.5, J10.14, J11.1, Q101.2 (S), Q106.2 (S), Q111.2 (S), Q131.2 (S), Q136.2 (S), Q141.2 (S), R1.2, R6.2, R7.2, R8.2, R9.2, R14.2, R15.2, R17.2, R18.2, R20.2, R22.2, R131.2, R136.2, R141.2, R145.2, R148.2, R161.2, R166.2, R171.2, R175.2, R178.2, TP3.1, U1.2 (GND), U1.3 (~CE), U2.2 (GND), U2.8 (STB), U3.2 (GND), U4.4 (~LDAC), U4.10 (VSS), U5.4 (V-), U6.1 (ADDR), U6.3 (GND), U7.4 (GND), U10.4 (GND), U11.4 (GND), U12.3 (GND), U13.3 (GND)
/GND_MOT_A: C101.2, C105.2, C109.2, D101.1 (A), D105.1 (A), D109.1 (A), J1.2, J3.2, J5.5, J5.8, R133.2, R138.2, R148.1, TP11.1
/GND_MOT_B: C151.2, C155.2, C159.2, D151.1 (A), D155.1 (A), D159.1 (A), J2.2, J4.2, J6.5, J6.8, R163.2, R168.2, R178.1, TP18.1
/HALL_A1: J10.5, U10.7
/HALL_A2: J10.4, U11.7
/HALL_B1: J10.6, U10.2
/HALL_B2: J10.7, U11.2
/HALL_C1: J10.3, U10.5
/HALL_C2: J10.8, U11.5
/HW_REV: C17.1, R21.2, R22.1, U6.7 (AIN3)
/I2C_SCL: J11.3, R12.2, U4.2 (SCL), U6.10 (SCL)
/I2C_SDA: J11.6, R11.2, U4.3 (SDA), U6.9 (SDA)
/LED_3V3: D3.2 (A), R3.2
/LED_5V: D2.2 (A), R2.2
/LED_EL_A: R23.1, U7.7
/LED_EL_A_K: D5.2 (A), R23.2
/LED_EL_B: R24.1, U7.2
/LED_EL_B_K: D6.2 (A), R24.2
/LED_SAFE: D7.1 (K), U7.5
/LED_SAFE_A: D7.2 (A), R25.2
/LED_STATUS: D8.1 (K), J11.16
/LED_STAT_A: D8.2 (A), R26.2
/MA_HA: J1.3, J3.3, R101.2, R102.1, TP7.1
/MA_HA_F: C101.1, D101.3 (COM), R102.2, U10.1
/MA_HB: J1.4, J3.4, R105.2, R106.1, TP8.1
/MA_HB_F: C105.1, D105.3 (COM), R106.2, U10.6
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
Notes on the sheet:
MODULE ESP32-DevKitC V4 (MOTION) — supports 2 × 19, entraxe 25,40 mm (P1)
DORSALE — J8/J9 en parallèle, anti-inversion, TVS, diode idéale vers le module
CAN — TCAN1042HVDR, STB à la masse, VIO 3,3 V, pas de terminaison sur cette carte
/SAFE — résistance série (nœud éteint non rétro-alimenté), 1 MΩ local (ICD SAFE_N_spec)
WATCHDOG — TPL5010 : RSTn sur EN de l'ESP32 (D7), intervalle 2 s
CONSIGNE VR — MCP4728 en 3,3 V (VIH = 0,7 VDD), réf. interne 2,048 V, TLV9062 gain 2,5
MESURES — ADS1115 (0x48) : NTC A, NTC B, rôle, révision matérielle
VOYANTS — tampon tolérant 5 V : frein serré A/B (sur EL), /SAFE actif ; LED d'état GPIO15
MOTEUR A — passage Hall J1→J3 métallique, prélèvement, commande J5
MOTEUR B — passage Hall J2→J4 métallique, prélèvement, commande J6
v2.0-draft — ne pas fabriquer avant M7, HALL_OC, P1, P2, P3
J7 (alimentation séparée) supprimé : 5 V par la dorsale uniquement (broche 1 de J8/J9).
J5/J6 broche 7 : NC (D5). Le pull-up 2,2 kΩ de EL vers 5V_BRAKE est SUR LE FAISCEAU, côté variateur.
Aucune option de peuplement sur EL. Options DIR/STOP non montées : R_PU (4,7k), R_PD (10k), R_DIRECT (1k).
R148/R178 (0 Ω GND_MOT–GND) : NON MONTÉES. Banc seulement, jamais sur le robot (D4).
Tampons Hall : SN74LVC3G17 uniquement (Ioff). Interdits : 74HC14, 74HCT14, SN74LVC14A.
MCP4728 : programmer l'EEPROM à 0 en production (VR = 0 V dès la mise sous tension).
Rôle (ADS1115 AIN2) : SJ1 ouvert = AVANT, SJ1 fermé = ARRIÈRE, SJ2 fermé = BANC.

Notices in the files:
README.md:
Licence: Apache 2.0
Hardware: CERN OHL S v2
hardware/pcb/motor_interface/kicad/motor_interface.kicad_sch:
Retriever, open hardware (CERN-OHL-S-2.0)
